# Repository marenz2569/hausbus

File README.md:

# Hausbus

## Configuration

The configuration xml file is saved in `config-creator/`. Its schema definition is saved in `config-creator/config.xsd`.

To generate the `.c` and `.h` files, saved in `src/`, execute `make CONFIG=[path to config file]`.

An example configuration is given in `config-creator/config.xml.example`.

### Functions

function | note | forbidden variable names | tested
--- | --- | --- | ---
button | execute code on press, unpress or click count events | el | :white_check_mark:
output |
pwm ||| :white_check_mark:
tick | code will be executed every 1ms | a, b, c | :white_check_mark:
code | add your own functions to the c file || :white_check_mark:
loop | add your own code to the loop otherwise the controller will be put to idle sleep mode; variables used here must be declared in the `init` function; do not write blocking code, otherwise can messages might not be read || :white_check_mark:
init | add your own code to the init || :white_check_mark:

## Building

Execute `make -j` to build all targets or execute `make -j TARGETS=[list of .c files]`.

## Bootloader

The nodes on the can bus can be flashed via the [can-bootloader from Fabian Greif][3].

## Debugging

- **check the fuses!**
- **check the slave select pin**

## Dependencies

* [Saxon 9.8][1]
* xmllint from libxml2
* [Zsh][2]
* gcc-avr
* binutils-avr
* avr-libc
* python3
* graphviz

[1]: https://sourceforge.net/projects/saxon/files/Saxon-HE/
[2]: http://zsh.sourceforge.org
[3]: http://www.kreatives-chaos.com/artikel/can-bootloader

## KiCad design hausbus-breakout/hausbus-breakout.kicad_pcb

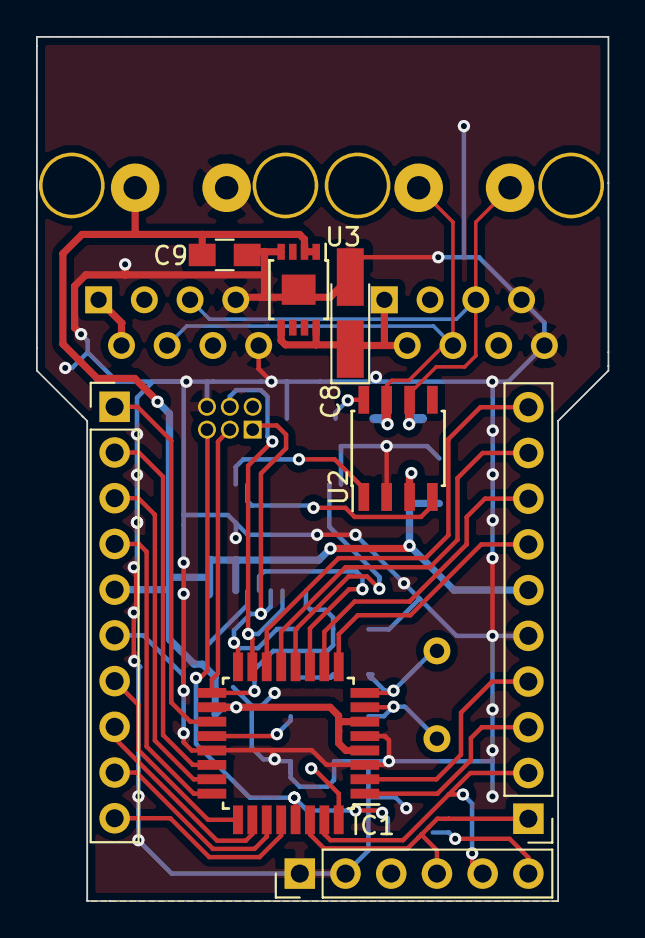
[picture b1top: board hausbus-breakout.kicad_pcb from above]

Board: 2 copper layers, 31.8 x 48.0 mm, 28 parts (0 on the bottom side), 37 nets.

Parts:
C1, C2, C7: 100nF; C_0805_HandSoldering
C3, C4: 22pF; C_0805_HandSoldering
C5, C6: 100n; C_0805_HandSoldering
C8: 1u; CP_Tantalum_Case-A_EIA-3216-18_Hand
C9: 1u; C_0805_HandSoldering
C10: 10n; C_0805_HandSoldering
CON1: AVR-ISP-6; Socket_Strip_Straight_2x03_Pitch1.27mm
IC1: ATMEGA328P-M; TQFP-32_7x7mm_Pitch0.8mm
J1, J2: RJ45; RJ45_8
P1, P2: CONN_01X10; Socket_Strip_Straight_1x10_Pitch2.54mm
P3, P4: CONN_01X02; 2_5.08mm
P5: CONN_01X06; Socket_Strip_Straight_1x06_Pitch2.54mm
R1: 120R; R_0805_HandSoldering
R2, R3: 10k; R_0805_HandSoldering
R4: 68k; R_0805_HandSoldering
R5: 1k; R_0805_HandSoldering
U1: MCP2515-I/ST; TSSOP-20_4.4x6.5mm_Pitch0.65mm
U2: PCA82C251; SOIC-8_3.9x4.9mm_Pitch1.27mm
U3: LT3010-5; MSOP-8-1EP_3x3mm_Pitch0.65mm
Y1: 16MHz; Crystal_HC49-U_Vertical

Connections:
+5V: C1.1, C2.1, C7.1, C9.1, IC1.4, IC1.6, IC1.18, P1.6, P2.5, P4.1, R2.1, R3.2, U1.20, U2.3, U3.1, U3.2
ADC6: IC1.19, P2.1
ADC7: IC1.22, P2.2
B1: IC1.13, P1.9
B2: IC1.14, P1.10
C0: IC1.23, P2.3
C1: IC1.24, P2.4
C2: IC1.25, P2.7
C3: IC1.26, P2.8
C4: IC1.27, P2.9
C5: IC1.28, P2.10
CAN+: J1.4, J2.4, P3.1, R1.2, U2.7
CAN-: J1.5, J2.5, P3.2, R1.1, U2.6
CLKO: IC1.12, U1.9
D0: IC1.30, P1.1, P5.4
D1: IC1.31, P1.2, P5.5
D3: IC1.1, P1.3
D4: IC1.2, P1.4
D5: IC1.9, P1.7
D6: IC1.10, P1.8
GND: C1.2, C2.2, C3.2, C4.2, C5.2, C7.2, C8.2, C9.2, CON1.6, IC1.3, IC1.5, IC1.21, J1.7, J1.8, J2.7, J2.8, P1.5, P2.6, P4.2, P5.1, P5.2, R4.1, U1.10, U2.2, U3.4, U3.9
INT0: IC1.32, U1.13
MISO: CON1.1, IC1.16, R5.2, U1.17
MOSI: CON1.4, IC1.15, U1.16
unnamed: C5.1, IC1.20
unnamed: C6.1, P5.6
unnamed: C10.2, R5.1
unnamed: R3.1, U1.19
unnamed: R4.2, U2.8
OSC1: C3.1, IC1.7, Y1.1
OSC2: C4.1, IC1.8, Y1.2
RS: C6.2, CON1.5, IC1.29, R2.2
RXD: U1.2, U2.4
SCK: C10.1, CON1.3, IC1.17, U1.14
SS: IC1.11, U1.18
TXD: U1.1, U2.1
VCOM: C8.1, J1.1, J1.2, J2.1, J2.2, U3.5, U3.8

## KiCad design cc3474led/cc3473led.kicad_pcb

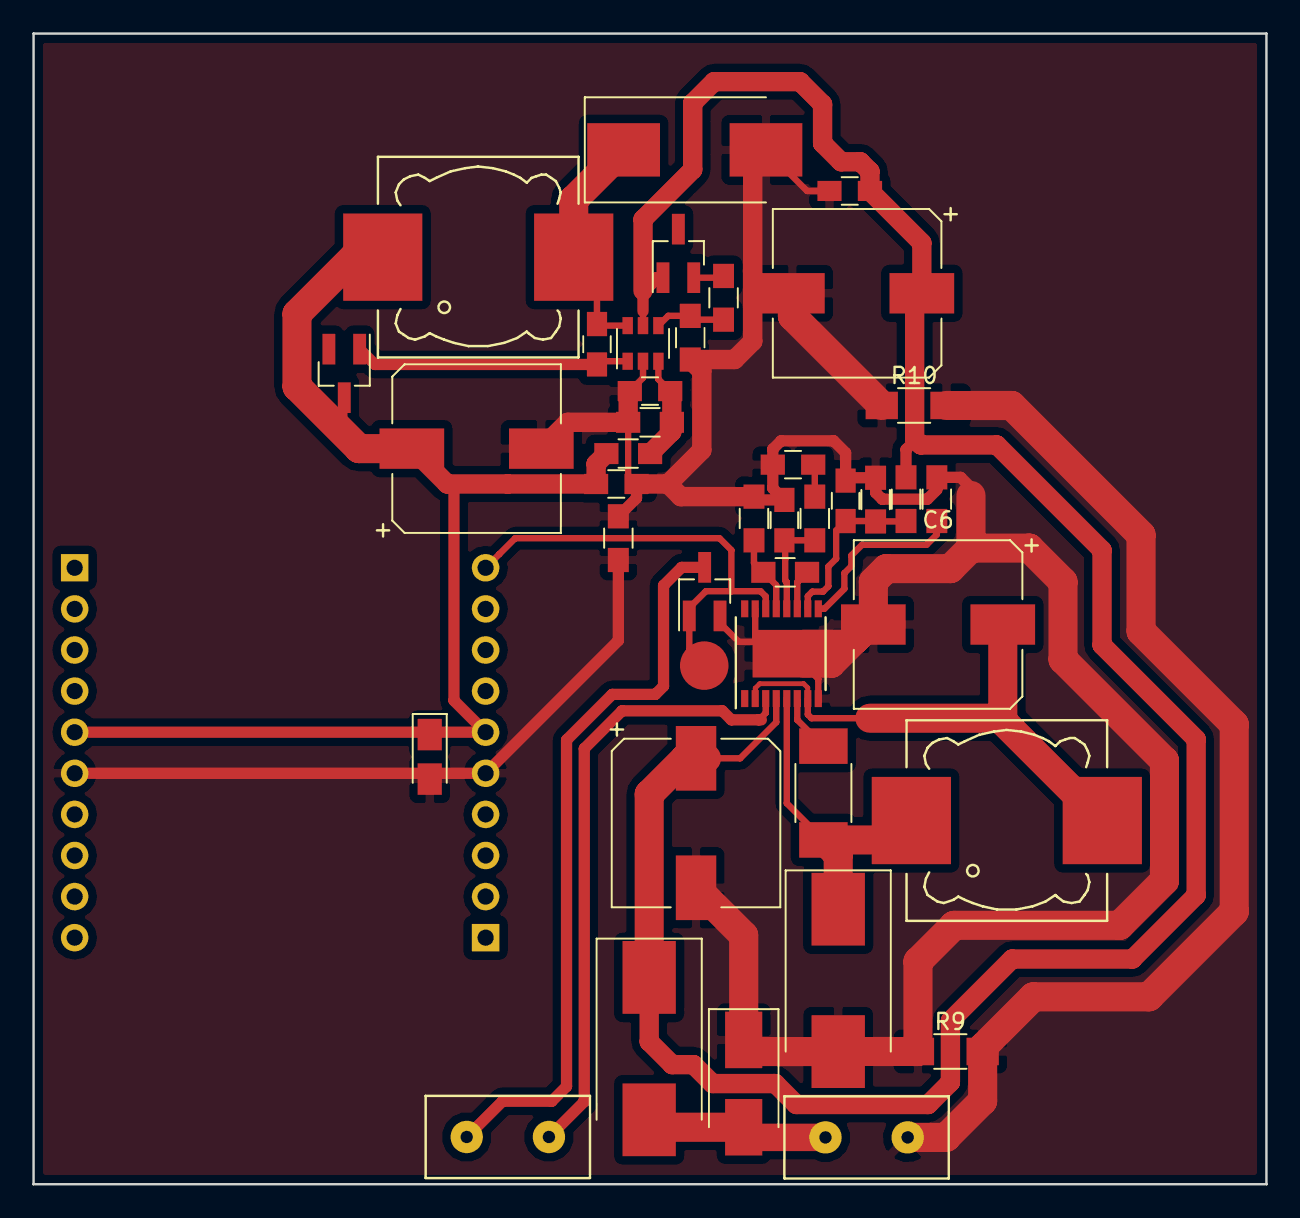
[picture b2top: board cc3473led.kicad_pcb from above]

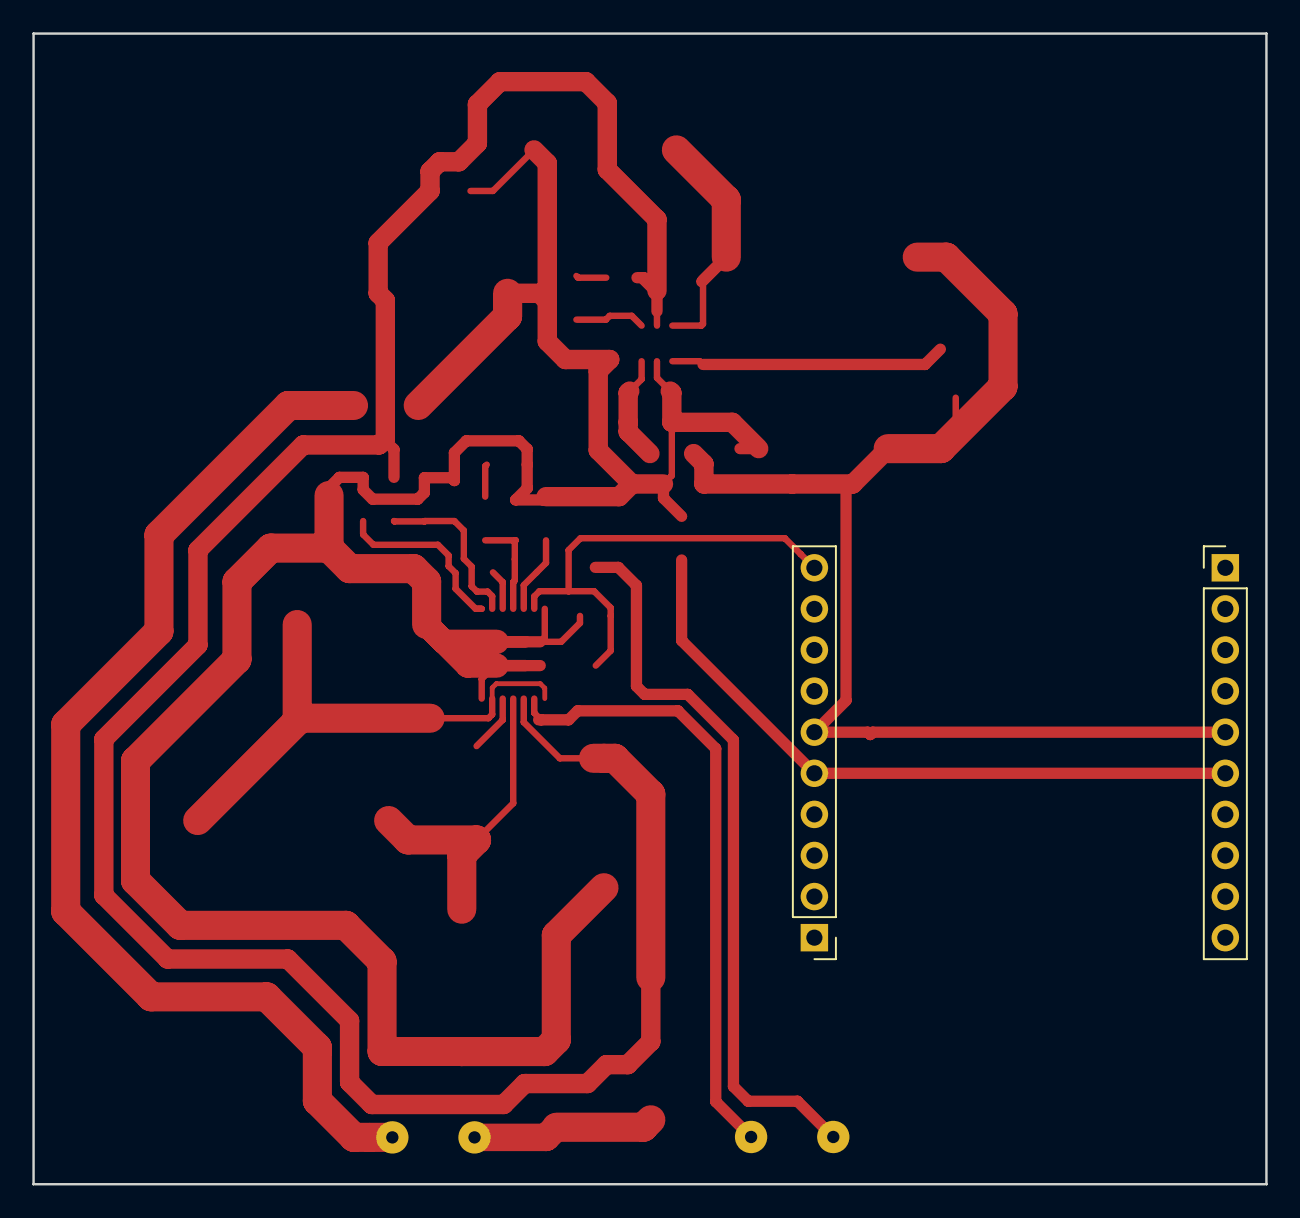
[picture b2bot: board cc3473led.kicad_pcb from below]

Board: 2 copper layers, 76.2 x 71.1 mm, 42 parts (2 on the bottom side), 21 nets.

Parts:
C1, C6, C7, C12: 100u; CP_Elec_10x10.5
C2: 1n; C_0805_HandSoldering
C3, C8, C9, C11: 100n; C_0805_HandSoldering
C4: 3.3n; C_0805_HandSoldering
C5: 2.2u; C_1812_HandSoldering
C10: n.b.; C_0805_HandSoldering
C13: 10u; CP_Tantalum_Case-A_EIA-3216-18_Reflow
D1, D3, D5: SK86; D_SMC_Handsoldering
D2: P6SMB30CA; D_SMB_Handsoldering
D4: BZX84C 8V2; SOT-23_Handsoldering
D6: BAS70-06; SOT-23_Handsoldering
IC1: LT3474; TSSOP-16-1EP_4.4x5mm_Pitch0.65mm
L1: L-PIS4728 47u; Choke_SMD_Wuerth-WE-PD-Typ-LS_Handsoldering
L2: L-PIS4728 33u; Choke_SMD_Wuerth-WE-PD-Typ-LS_Handsoldering
P1: PWM; Measurement_Point_Round-SMD-Pad_Big
P2, P5: CONN_01X02; 2_5.08mm
P3, P4: CONN_01X10; Socket_Strip_Straight_1x10_Pitch2.54mm
Q1: IRLM0060; SOT-23_Handsoldering
R1: R_adj_2; R_0805_HandSoldering
R2: 82k; R_0805_HandSoldering
R3: 100k; R_0805_HandSoldering
R4: 27k; R_0805_HandSoldering
R5: R_adj_1; R_0805_HandSoldering
R6, R7, R8: 10k; R_0805_HandSoldering
R9, R10: 0R; R_1206_HandSoldering
R11: 0R; R_0805_HandSoldering
R_bot1: 8k2; R_0805_HandSoldering
R_top1: 43k; R_0805_HandSoldering
U1: MCP16331; SOT-23-6

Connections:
+5V: C11.1, C12.1, C13.1, D6.3, L2.1, P3.6, P4.5, R_top1.1
/Constant Current Regulator/LED+: IC1.3, P2.1
/Constant Current Regulator/LED-: P2.2, Q1.3
/PWM: IC1.14, P1.1, P3.10, Q1.1
/Power Protection/V_IN: D2.2, D3.2, P5.2
GND: C1.2, C2.2, C3.1, C4.1, C6.2, C7.2, C8.2, C10.2, C11.2, C12.2, C13.2, D1.2, D2.1, D5.2, IC1.8, IC1.15, IC1.17, P3.5, P4.6, P5.1, Q1.2, R1.1, R2.1, R4.1, R8.1, R9.1, R9.2, R10.1, R10.2, R11.1, R11.2, R_bot1.2, U1.2
unnamed: C2.1, IC1.10, R3.2, R4.2
unnamed: C3.2, R6.1
unnamed: C4.2, IC1.12, R6.2
unnamed: C5.1, IC1.6
unnamed: C5.2, D1.1, IC1.5, L1.1
unnamed: C6.1, IC1.2, IC1.7, L1.2
unnamed: C9.1, D5.1, L2.2, U1.6
unnamed: C9.2, D6.1, U1.1
unnamed: C10.1, R_bot1.1, R_top1.2, U1.3
unnamed: D4.2, R7.2
unnamed: IC1.9, R2.2
unnamed: IC1.11, R5.1
unnamed: IC1.13, R1.2, R5.2
unnamed: R7.1, R8.2, U1.4
VCOM: C1.1, C7.1, C8.1, D3.1, D4.1, IC1.4, R3.1, U1.5

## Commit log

2016-10-18 added gitignore
2016-10-18 added mcp2515 lib
2016-10-19 not including 'src/handler.h'; this file will get generated on build
2016-10-19 makefile for building source
2016-10-19 added code
2016-10-19 added extra code to lib subdirectory
2016-10-19 added submodule
2016-10-19 removed old handler file
2016-10-20 added new version of mcp2515 lib
2016-10-20 now getting the right can id
2016-10-20 change pin
2016-10-20 always rebuilding user specific object files
2016-10-20 added uart lib
2016-10-20 added programm to sniff can bus and print frames to uart
2016-10-20 removed showing data with remote frames
2016-10-20 removed execution of commands in LAMP1_handler if it is a remote frame
2016-10-21 removed broken parts
2016-10-31 can_print does now send messages to uart in json format
2016-10-31 added new mode for LAMP protocol
2016-10-31 added code for pwm
2016-10-31 changed header for pwm code
2016-10-31 added code for asyncronus delays
2016-10-31 add new objects to makefile
2016-10-31 removed temporary default value in pwm_init function
2016-10-31 moved pwm variable; fixed pwm frequency
2016-10-31 fixed multiple excution of code
2016-10-31 add functions for pwm incrementation, decrementation and setting a specific value
2016-10-31 added macros for ports
2016-10-31 fixed bug in pwm_dec function
2016-10-31 added function for getting pwm value
2016-10-31 fix: pwm value 255 is now always on
2016-11-02 don't delete *.elf file after build
2016-11-02 made makefile foo clearer
2016-11-03 not deleting *.elf files anymore
2016-11-25 removed redundand code; changed case ON to SWITCH
2016-11-26 removed unnessesary hausbus_handler()
2016-11-26 target can now be directory to a source file
2016-11-26 automatically getting targets now
2016-12-27 using __flash insted of PROGMEM, because it is neater and easier to use
2017-05-15 fixed bugs; removed old structures; added user tick interrupt
2017-05-15 *(x) to *x
2017-05-15 updated examples
2017-05-15 added module switch
2017-05-28 mcp2515 io is ignored
2017-05-28 modified pwm
2017-05-28 switch to output and some changes
2017-05-28 added module for buttons
2017-05-28 tick changes
2017-05-28 faster baudrate
2017-05-28 removed examples
2017-05-28 modified can_print
2017-05-28 updated makefile
2017-05-28 updated gitignore for python env
2017-05-28 added python script creating firmware sources based on xml configuration file
2017-05-28 remove every elf, hex or o file
2017-05-28 new version of mcp2515 library
2017-05-28 new gitignore for kicad
2017-05-28 library for RDN Connectors
2017-05-28 added breakout
2017-05-31 changed fuses; remove unused code
2017-05-31 increased frequency; safe change of values possible
2017-05-31 removed bug: OUTPUT_TOGGLE is now working
2017-05-31 dimming works with long presses!
2017-05-31 updated config-creator to latest code changes
2017-06-05 droped the idea of software pwm. using timer 0 and 1 with their 4 hardware pwm channels.
2017-06-05 cleanup
2017-06-05 did not include all backup files
2017-06-05 updated breakout to have all four hardware pwm pins of timer 0 and 1 available
2017-06-05 added config file for library
2017-06-05 updated auxillary functions for pwm
2017-06-06 updated constant length of can message
2017-06-06 ss pin must be used as an output
2017-06-06 C6 is used as reset
2017-06-18 added usb2serial converter header
2017-06-18 added board with lt3474 constant current pwm led regulator
2017-06-29 save state of required modules in eeprom
2017-07-01 exchanged ugly python script to a nice xslt file
2017-07-01 python stuff is not necessary anymore
2017-07-02 don't include files generated from config
2017-07-02 move examples to their own folder
2017-07-06 created example folder
2017-07-06 moved lib directory
2017-07-06 removed nasty file
2017-07-06 do not save .xml config files
2017-07-06 moved saxon9.8
2017-07-09 added dependencies to readme
2017-07-10 added configuration in readme
2017-07-10 spelling correction
2017-07-24 new tools for uart_to_vcan gateway
2017-08-01 cleanup of schematic, added rj45 jacks for can bus
2017-08-12 changed resistor values
2017-08-12 changed size of 0R resistors
2017-08-15 changed env directory
2017-08-15 specified relative path to directory
2017-08-15 added debugging section
2017-08-15 added exceptions
2017-08-15 added power on message
2017-08-15 added function output_save to save all locks and values to eeprom
2017-08-15 prevention: rename eeprom varibles with module name prefix
2017-08-15 added function to save eeprom variables of pwm module
2017-08-16 bug fixed
2017-08-23 removed comment
2017-09-01 added tick element in xml configuration
2017-09-01 added code element in xml configuration
2017-10-22 bug fix
2017-11-14 added python script for generating program callgraphs
2017-11-14 changed function name
2017-11-14 updated Makefiles cleaning function
2017-11-14 add *.ps to .gitignore
2017-11-20 better description xsd document and renamed libraries to functions
2017-11-21 updated functions segment in readme file
2017-11-21 Makefile: discard errors from ls, fixed clean section and added config-clean section
2017-11-24 fixed: shortpress count was one to high on every long press
2017-11-25 fixed: not recompiling mcp2515.c file if its config has been changed
2017-11-26 added ss attribute to xml configuration for selection of slave select pin of mcp2515
2017-11-27 merged with input- with outputpins type to generalpins type
2017-12-01 fix spelling
2017-12-01 deleted unnecessary function argument
2017-12-01 change of last commit
2017-12-01 added press and unpress events
2017-12-01 fixed schema definition error
2017-12-01 added loop function
2017-12-01 added init function
2017-12-01 added support for NC buttons
2017-12-02 added note to loop function in README
2017-12-10 changed efuse to 0xff
2017-12-11 new version of mcp2515 lib with receive buffer
2017-12-11 many changes have been done to the breakout
2017-12-11 now polling each packet from internal buffer
2017-12-11 do not configure ddb2
2017-12-11 added tested column to function table in readme
2017-12-11 added note
2017-12-17 fixed 1ms timer to trigger every 1ms and not interfere with timer 0
2017-12-17 pwm module is working
2017-12-17 value in wrong column
2017-12-28 added debugging information
2018-02-08 added id 100 to save eeprom on every device
2018-02-08 optimized Makefile for parallel compiling (with -j option of make)
2018-02-08 eeprom will now be written to mcu and checked by program
2018-02-16 added bootloader. make does now work with -j flag
2018-02-16 accidentally changed
2018-02-16 added information for the bootloader. updated information for the configuration
2018-02-16 changed bootloader-can remote
2018-02-16 updated bootloader
2018-02-17 do not compile bootloader with MFLAGS or MAKEFLAGS. deleted callgraph. compiler optimization.
2018-02-17 update of README
